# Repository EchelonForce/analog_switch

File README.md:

# Eurorack Analog Switch Module

This is a design for a eurorack module that puts an analog switch in the audio path.

Full writeup here: https://www.robotdialogs.com/2023/01/eurorack-analog-switch-module.html

This work is licensed under a Creative Commons Attribution-NonCommercial-ShareAlike 4.0 International License. https://creativecommons.org/licenses/by-nc-sa/4.0/

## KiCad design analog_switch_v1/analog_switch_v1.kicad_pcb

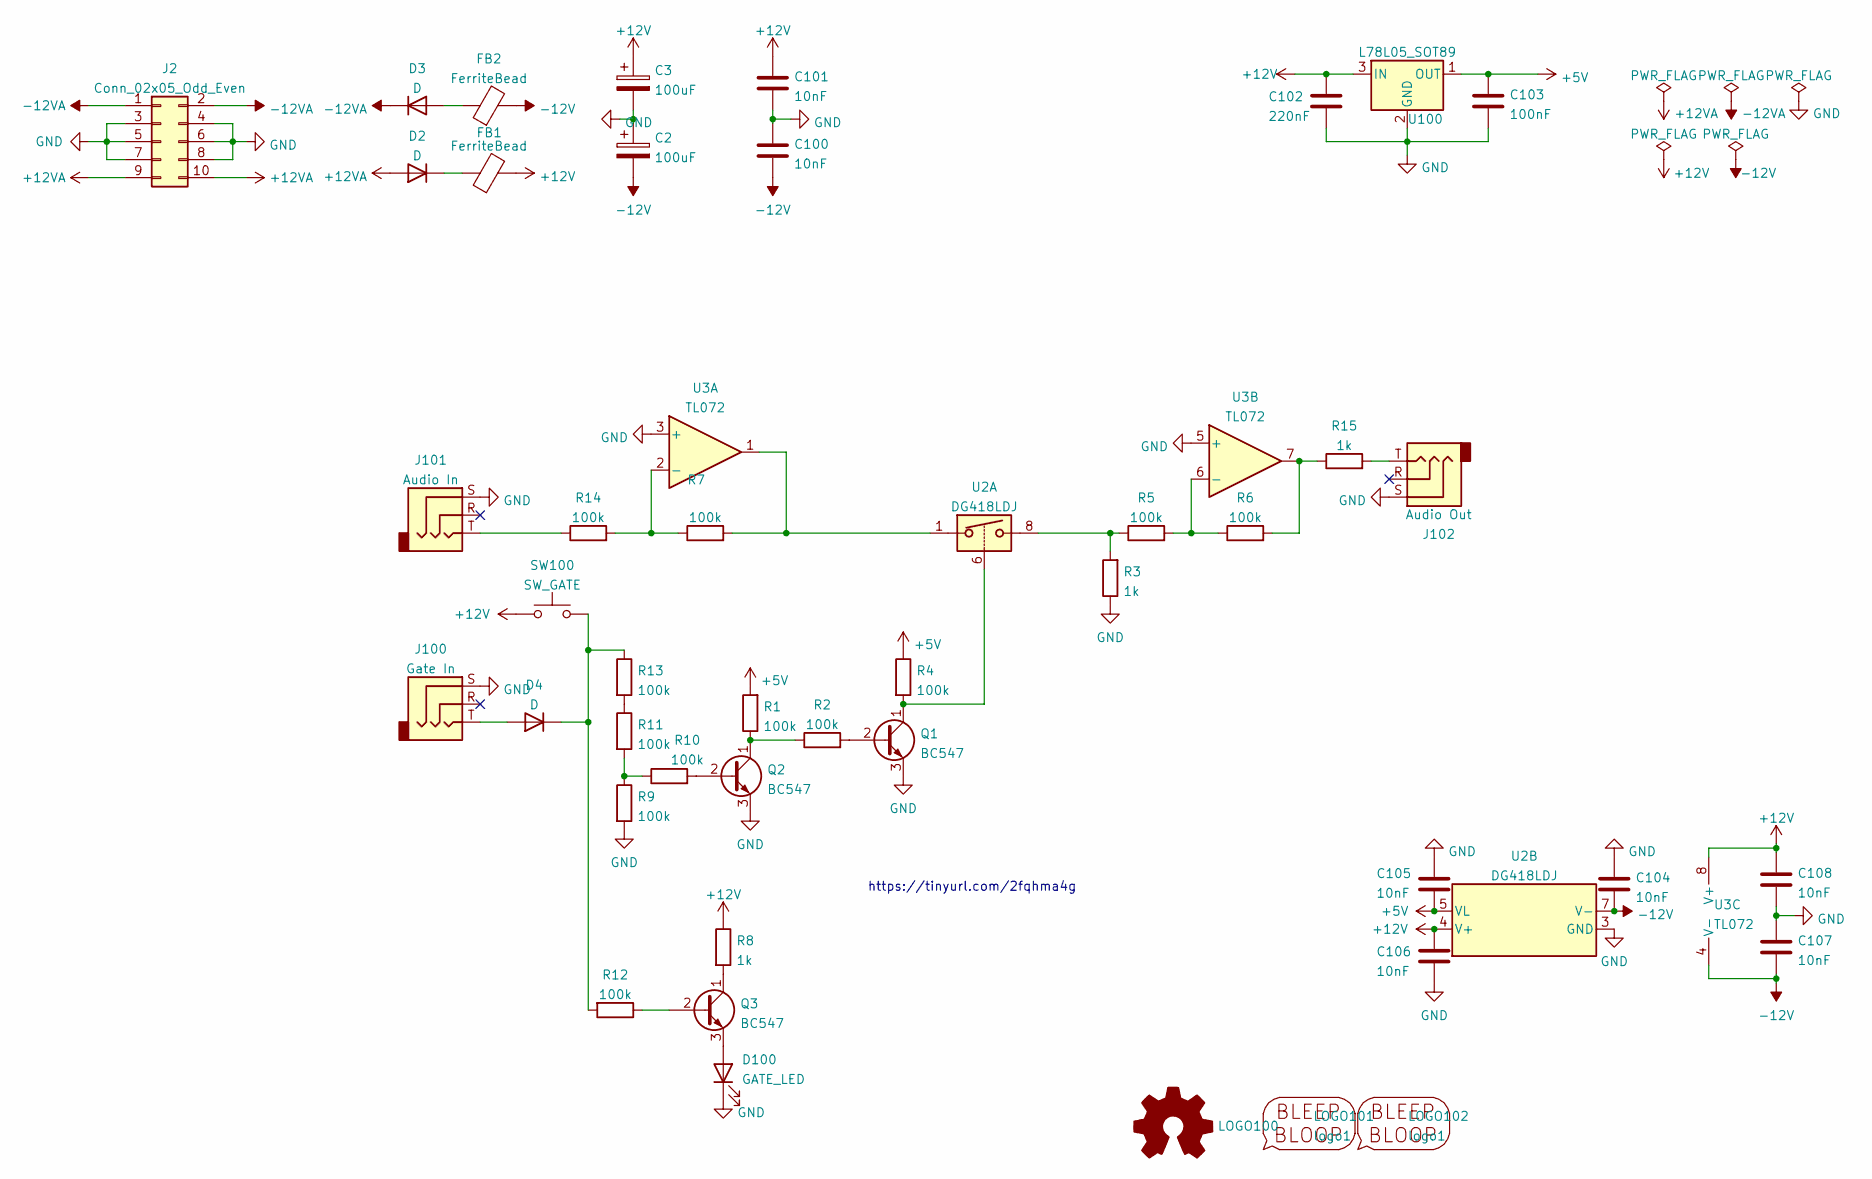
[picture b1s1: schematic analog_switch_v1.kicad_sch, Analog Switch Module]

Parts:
C2, C3: 100uF; CP_Radial_D5.0mm_P2.50mm
C100, C101, C104, C105, C106, C107, C108: 10nF; C_1206_3216Metric_Pad1.33x1.80mm_HandSolder
C102: 220nF; C_1206_3216Metric_Pad1.33x1.80mm_HandSolder
C103: 100nF; C_1206_3216Metric_Pad1.33x1.80mm_HandSolder
D2, D3, D4: D; D_A-405_P2.54mm_Vertical_KathodeUp
D100: GATE_LED; LED_D3.0mm
FB1, FB2: FerriteBead; L_Axial_L6.6mm_D2.7mm_P2.54mm_Vertical_Vishay_IM-2
J2: Conn_02x05_Odd_Even; IDC-Header_2x05_P2.54mm_Vertical
J100: Gate In; Jack_3.5mm_MJ-355W_Vertical
J101: Audio In; Jack_3.5mm_MJ-355W_Vertical
J102: Audio Out; Jack_3.5mm_MJ-355W_Vertical
LOGO100: Logo_Open_Hardware_Small; OSHW-Symbol_6.7x6mm_SilkScreen
LOGO101: logo1; Logo1
LOGO102: logo1; Logo2
Q1, Q2, Q3: BC547; TO-92_Inline_Wide
R1, R2, R4, R5, R6, R7, R9, R10, R11, R12, R13, R14: 100k; R_1206_3216Metric_Pad1.30x1.75mm_HandSolder
R3, R8, R15: 1k; R_1206_3216Metric_Pad1.30x1.75mm_HandSolder
SW100: SW_GATE; SW_PS1024ALRED
U2: DG418LDJ; DIP-8_W7.62mm_Socket_LongPads
U3: TL072; DIP-8_W7.62mm_Socket_LongPads
U100: L78L05_SOT89; SOT-89-3

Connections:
+5V: C103.1, C105.2, R1.2, R4.1, U2.5 (VL), U100.1 (OUT)
+12V: C3.1, C101.1, C102.1, C106.1, C108.1, FB1.2, R8.1, SW100.1, U2.4 (V+), U3.8 (V+), U100.3 (IN)
+12VA: D2.2 (A), J2.9, J2.10
-12V: C2.2, C100.2, C104.2, C107.2, FB2.2, U2.7 (V-), U3.4 (V-)
-12VA: D3.1 (K), J2.1, J2.2
GND: C2.1, C3.2, C100.1, C101.2, C102.2, C103.2, C104.1, C105.1, C106.2, C107.1, C108.2, D100.1 (K), J2.3, J2.4, J2.5, J2.6, J2.7, J2.8, J100.S, J101.S, J102.S, Q1.3 (E), Q2.3 (E), R3.1, R9.2, U2.3 (GND), U3.3 (+), U3.5 (+), U100.2 (GND)
unnamed: D2.1 (K), FB1.1
unnamed: D3.2 (A), FB2.1
unnamed: D4.1 (K), R12.2, R13.1, SW100.2
unnamed: D4.2 (A), J100.T
unnamed: D100.2 (A), Q3.3 (E)
unnamed: J101.T, R14.1
unnamed: J102.T, R15.2
unnamed: Q1.1 (C), R4.2, U2.6
unnamed: Q1.2 (B), R2.2
unnamed: Q2.1 (C), R1.1, R2.1
unnamed: Q2.2 (B), R10.2
unnamed: Q3.1 (C), R8.2
unnamed: Q3.2 (B), R12.1
unnamed: R3.2, R5.1, U2.8
unnamed: R11.1, R13.2
unnamed: R9.1, R10.1, R11.2
unnamed: R7.2, U2.1, U3.1
unnamed: R7.1, R14.2, U3.2 (-)
unnamed: R5.2, R6.1, U3.6 (-)
unnamed: R6.2, R15.1, U3.7

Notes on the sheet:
https://tinyurl.com/2fqhma4g

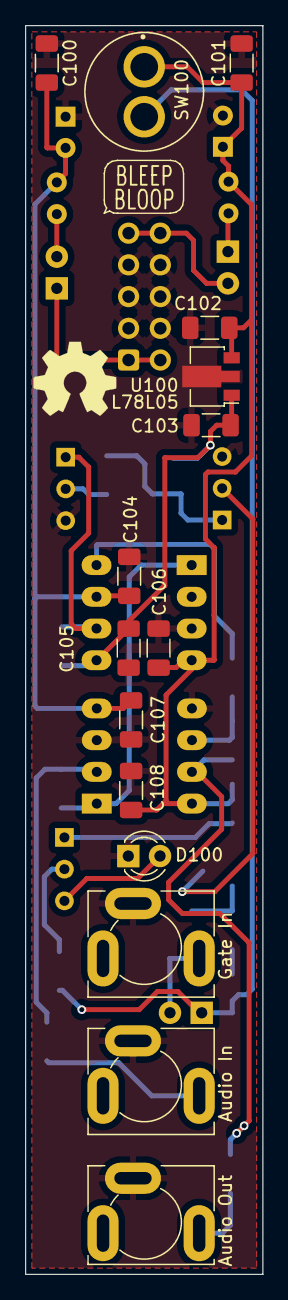
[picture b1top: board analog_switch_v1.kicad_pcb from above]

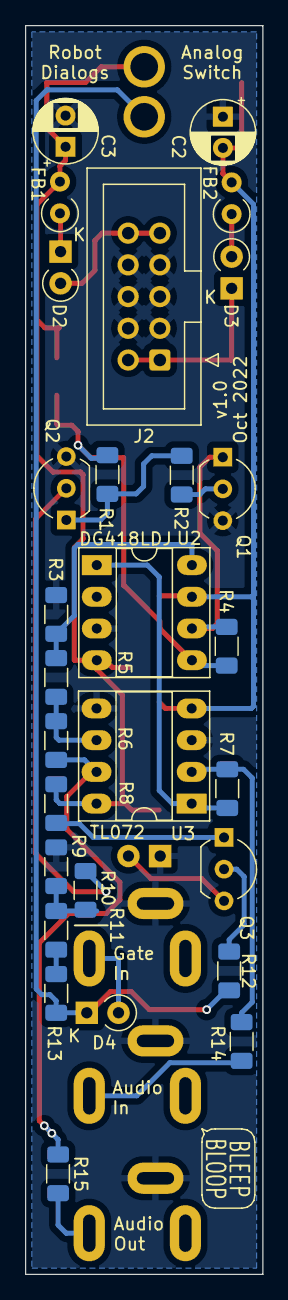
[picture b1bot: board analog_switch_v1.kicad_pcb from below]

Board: 2 copper layers, 19.0 x 100.0 mm, 46 parts (28 on the bottom side), 26 nets.

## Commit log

2022-10-08 Initial commit with .gitignore
2022-10-08 Schematic and PCB draft, not completed
2022-10-10 Geographic re-annotate and silkscreen cleanup
2022-10-10 Panelized v1
2022-10-15 Tried to fix mystery fusion pcb issue
    These boards had some issue when I ordered them, something in the
    fusion pcb service didn't work right but I don't know what... So I
    tweaked the silkscreen a bit and fixed the grid/drill origin. The
    single pcb works in their system but it still complained about the
    panelized version. I just submitted it anyways, we'll see if they find
    some more specific issue.
2022-10-15 Schematic pdf
2023-01-18 Add front panel CAD v1
2023-01-18 Notes update
2023-01-18 Add writeup link to README
